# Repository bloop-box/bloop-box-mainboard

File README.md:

# Bloop Box Mainboard

[Documentation](https://bloop-box.github.io/bloop-box-mainboard)

The board is designed using KiCAD 6 with production and assembly by JLCPCB in mind. All parts are selected to be
available from JLCPCB at the time of writing and as many parts as possible are used from their basic library.

- uHAT format (fits on a Raspberry Pi Zero)
- Connectors for:
  - Tailboard (Power supply, buttons, LEDs)
  - SPI NFC-reader (Pinout fitting for *RC522* Module)
  - Speaker
  - I2C connector for LED-Board
  - Additional GPIO header with UART (optional)
- Speaker is driven by a MAX98357 3W amplifier
  - amplifier gain can be set through jumper (9dB default setting)
  - SD_MODE is set to stereo mix by default, solder jumper for setting left-only 

Pinout of all connectors is printed on the bottom of the board

See schematics for detailed GPIO pinout

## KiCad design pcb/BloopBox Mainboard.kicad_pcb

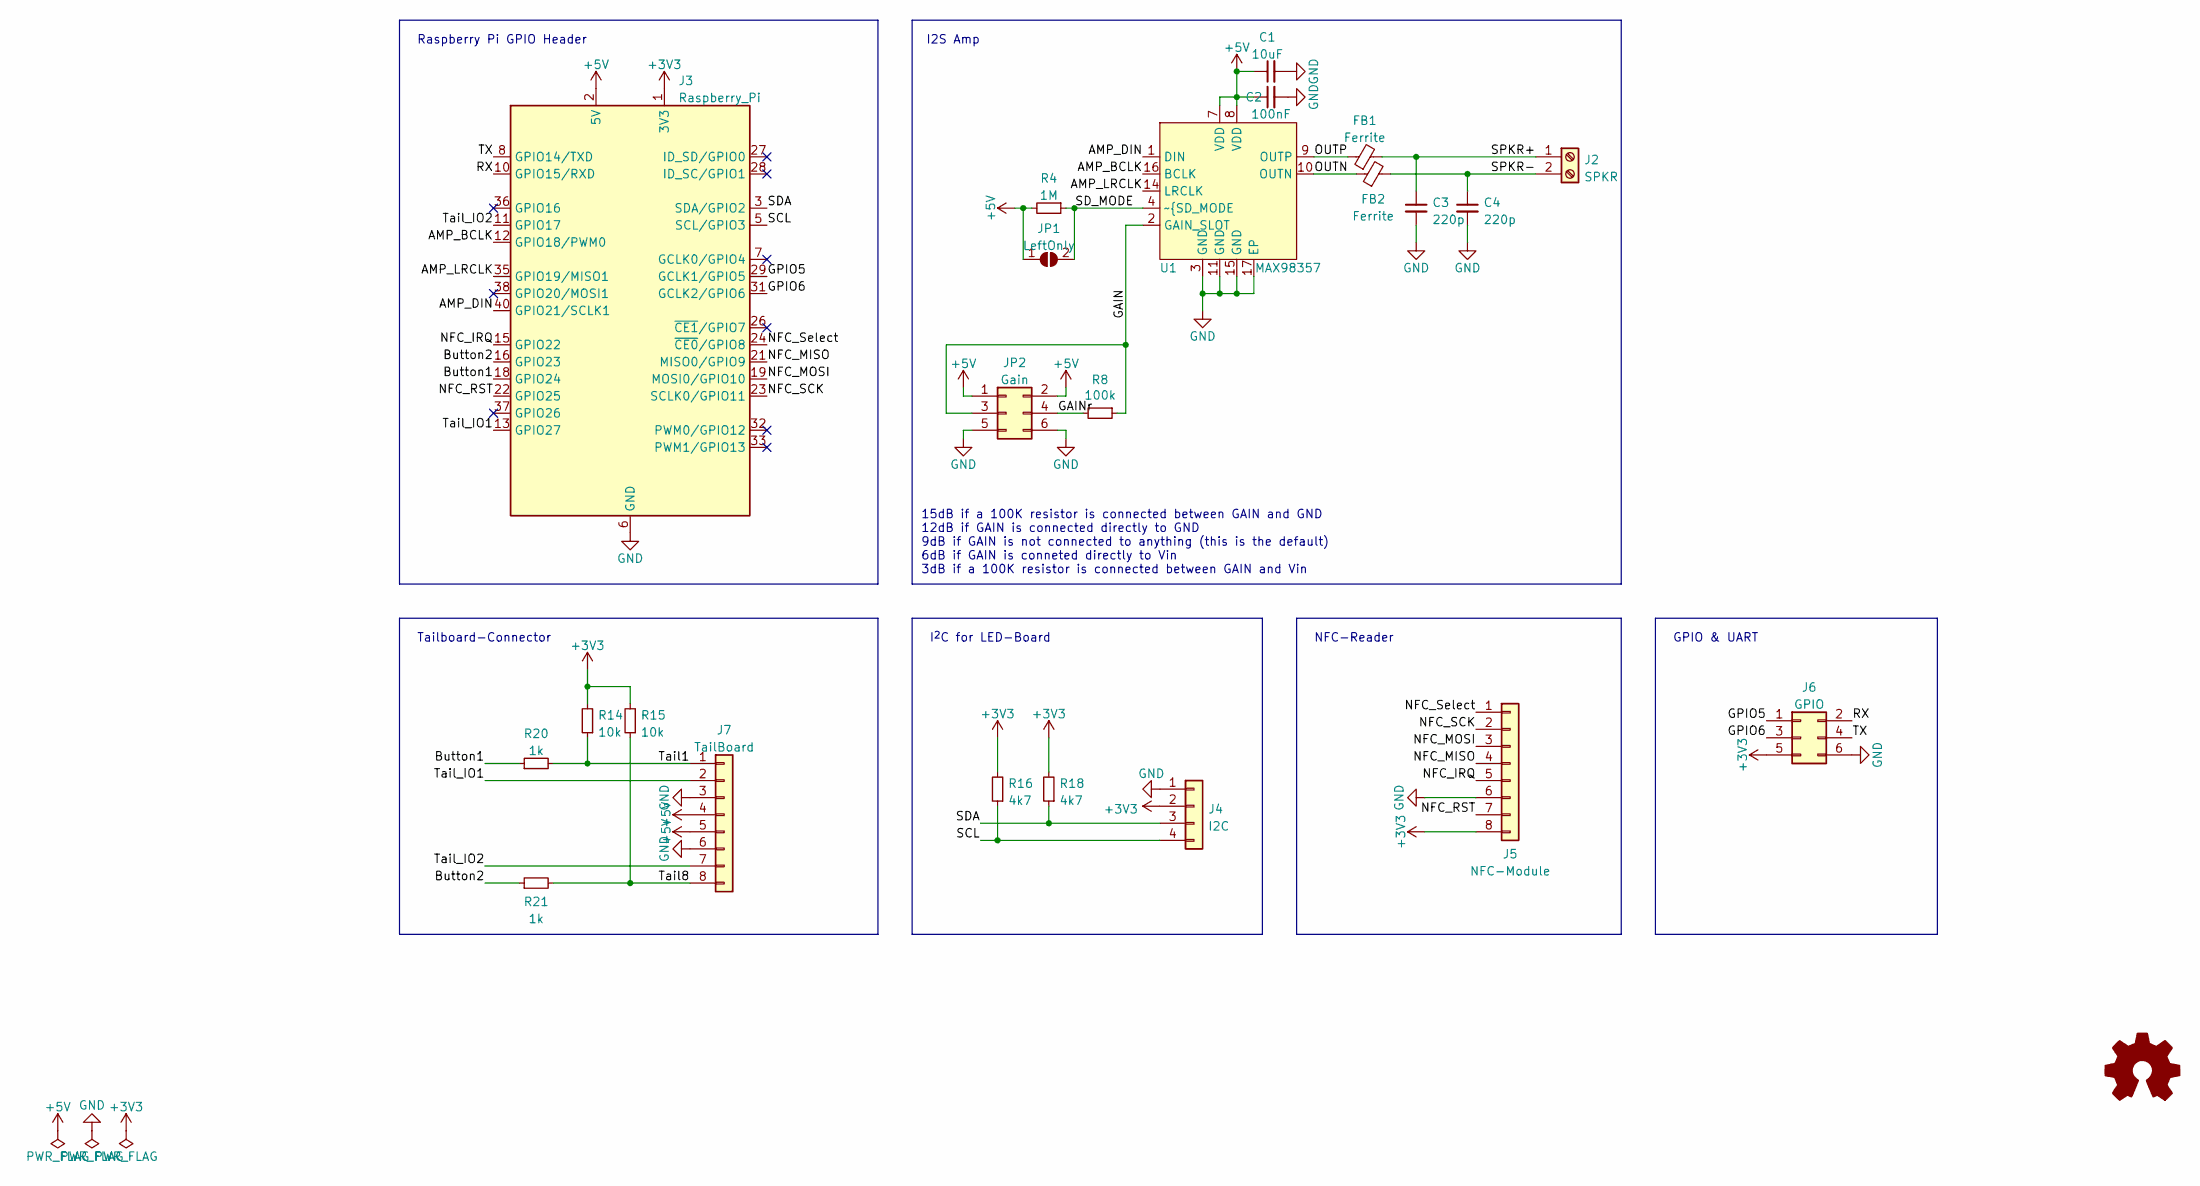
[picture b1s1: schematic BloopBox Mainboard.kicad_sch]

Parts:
C1: 10uF; C_0805_2012Metric; LCSC C15850
C2: 100nF; C_0402_1005Metric; LCSC C1525
C3, C4: 220p; C_0402_1005Metric; LCSC C1530
FB1, FB2: Ferrite; L_0805_2012Metric; LCSC C1015
J2: SPKR; JST_PH_S2B-PH-K_1x02_P2.00mm_Horizontal; LCSC C49992
J3: Raspberry_Pi; Raspberry_Pi_Zero_Socketed_THT_FaceDown_MountingHoles; LCSC C2977589
J4: I2C; JST_PH_S4B-PH-K_1x04_P2.00mm_Horizontal; LCSC C49994
J5: NFC-Module; JST_PH_S8B-PH-K_1x08_P2.00mm_Horizontal; LCSC C20598766
J6: GPIO; PinHeader_2x03_P2.54mm_Horizontal; LCSC C239334
J7: TailBoard; JST_PH_S8B-PH-K_1x08_P2.00mm_Horizontal; LCSC C20598766
JP1: LeftOnly; SolderJumper-2_P1.3mm_Open_RoundedPad1.0x1.5mm
JP2: Gain; PinHeader_2x03_P2.00mm_Vertical; LCSC C225288
R4: 1M; R_0402_1005Metric; LCSC C26083
R8: 100k; R_0402_1005Metric; LCSC C25741
R14, R15: 10k; R_0402_1005Metric; LCSC C25744
R16, R18: 4k7; R_0402_1005Metric; LCSC C25900
R20, R21: 1k; R_0402_1005Metric; LCSC C11702
U1: MAX98357; TQFN-16-1EP_3x3mm_P0.5mm_EP1.23x1.23mm_ThermalVias; LCSC C910544

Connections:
+3V3: J3.1 (3V3), J3.17 (3V3), J4.2, J5.8, J6.5, R14.2, R15.2, R16.2, R18.2
+5V: C1.1, C2.1, J3.2 (5V), J3.4 (5V), J7.4, J7.5, JP1.1 (A), JP2.1, JP2.2, R4.2, U1.7 (VDD), U1.8 (VDD)
/AMP_BCLK: J3.12 (GPIO18/PWM0), U1.16 (BCLK)
/AMP_DIN: J3.40 (GPIO21/SCLK1), U1.1 (DIN)
/AMP_LRCLK: J3.35 (GPIO19/MISO1), U1.14 (LRCLK)
/Button1: J3.18 (GPIO24), R20.1
/Button2: J3.16 (GPIO23), R21.1
/GAIN: JP2.3, R8.1, U1.2 (GAIN_SLOT)
/GAINr: JP2.4, R8.2
/GPIO5: J3.29 (GCLK1/GPIO5), J6.1
/GPIO6: J3.31 (GCLK2/GPIO6), J6.3
/NFC_IRQ: J3.15 (GPIO22), J5.5
/NFC_MISO: J3.21 (MISO0/GPIO9), J5.4
/NFC_MOSI: J3.19 (MOSI0/GPIO10), J5.3
/NFC_RST: J3.22 (GPIO25), J5.7
/NFC_SCK: J3.23 (SCLK0/GPIO11), J5.2
/NFC_Select: J3.24 (~CE0/GPIO8), J5.1
/OUTN: FB2.1, U1.10 (OUTN)
/OUTP: FB1.1, U1.9 (OUTP)
/RX: J3.10 (GPIO15/RXD), J6.2
/SCL: J3.5 (SCL/GPIO3), J4.4, R16.1
/SDA: J3.3 (SDA/GPIO2), J4.3, R18.1
/SD_MODE: JP1.2 (B), R4.1, U1.4 (~{SD_MODE)
/SPKR+: C3.1, FB1.2, J2.1
/SPKR-: C4.1, FB2.2, J2.2
/TX: J3.8 (GPIO14/TXD), J6.4
/Tail1: J7.1, R14.1, R20.2
/Tail8: J7.8, R15.1, R21.2
/Tail_IO1: J3.13 (GPIO27), J7.2
/Tail_IO2: J3.11 (GPIO17), J7.7
GND: C1.2, C2.2, C3.2, C4.2, J3.6 (GND), J3.9 (GND), J3.14 (GND), J3.20 (GND), J3.25 (GND), J3.30 (GND), J3.34 (GND), J3.39 (GND), J4.1, J5.6, J6.6, J7.3, J7.6, JP2.5, JP2.6, U1.3 (GND), U1.11 (GND), U1.15 (GND), U1.17 (EP)

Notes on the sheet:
I^{2}C for LED-Board
Raspberry Pi GPIO Header
GPIO & UART
I2S Amp
Tailboard-Connector
15dB if a 100K resistor is connected between GAIN and GND 12dB if GAIN is connected directly to GND 9dB if GAIN is not connected to anything (this is the default) 6dB if GAIN is conneted directly to Vin 3dB if a 100K resistor is connected between GAIN and Vin
NFC-Reader

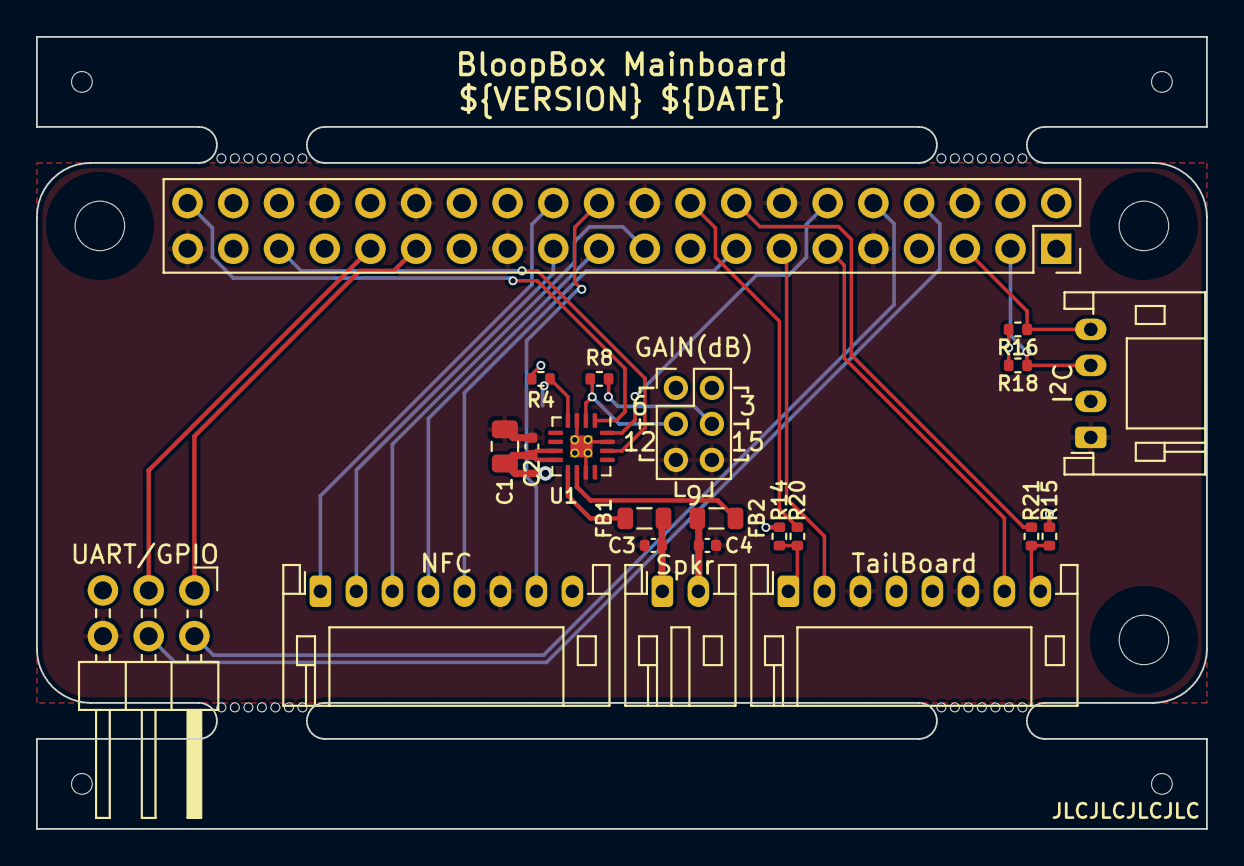
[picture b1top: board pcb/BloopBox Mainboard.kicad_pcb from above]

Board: 2 copper layers, 65.0 x 44.0 mm, 27 parts (1 on the bottom side), 31 nets.

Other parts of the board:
mouse-bite-2mm-slot, mouse-bite-2mm-slot#2, mouse-bite-2mm-slot#3, mouse-bite-2mm-slot#4: VAL**; mouse-bite-2x5mm-slot-onesided

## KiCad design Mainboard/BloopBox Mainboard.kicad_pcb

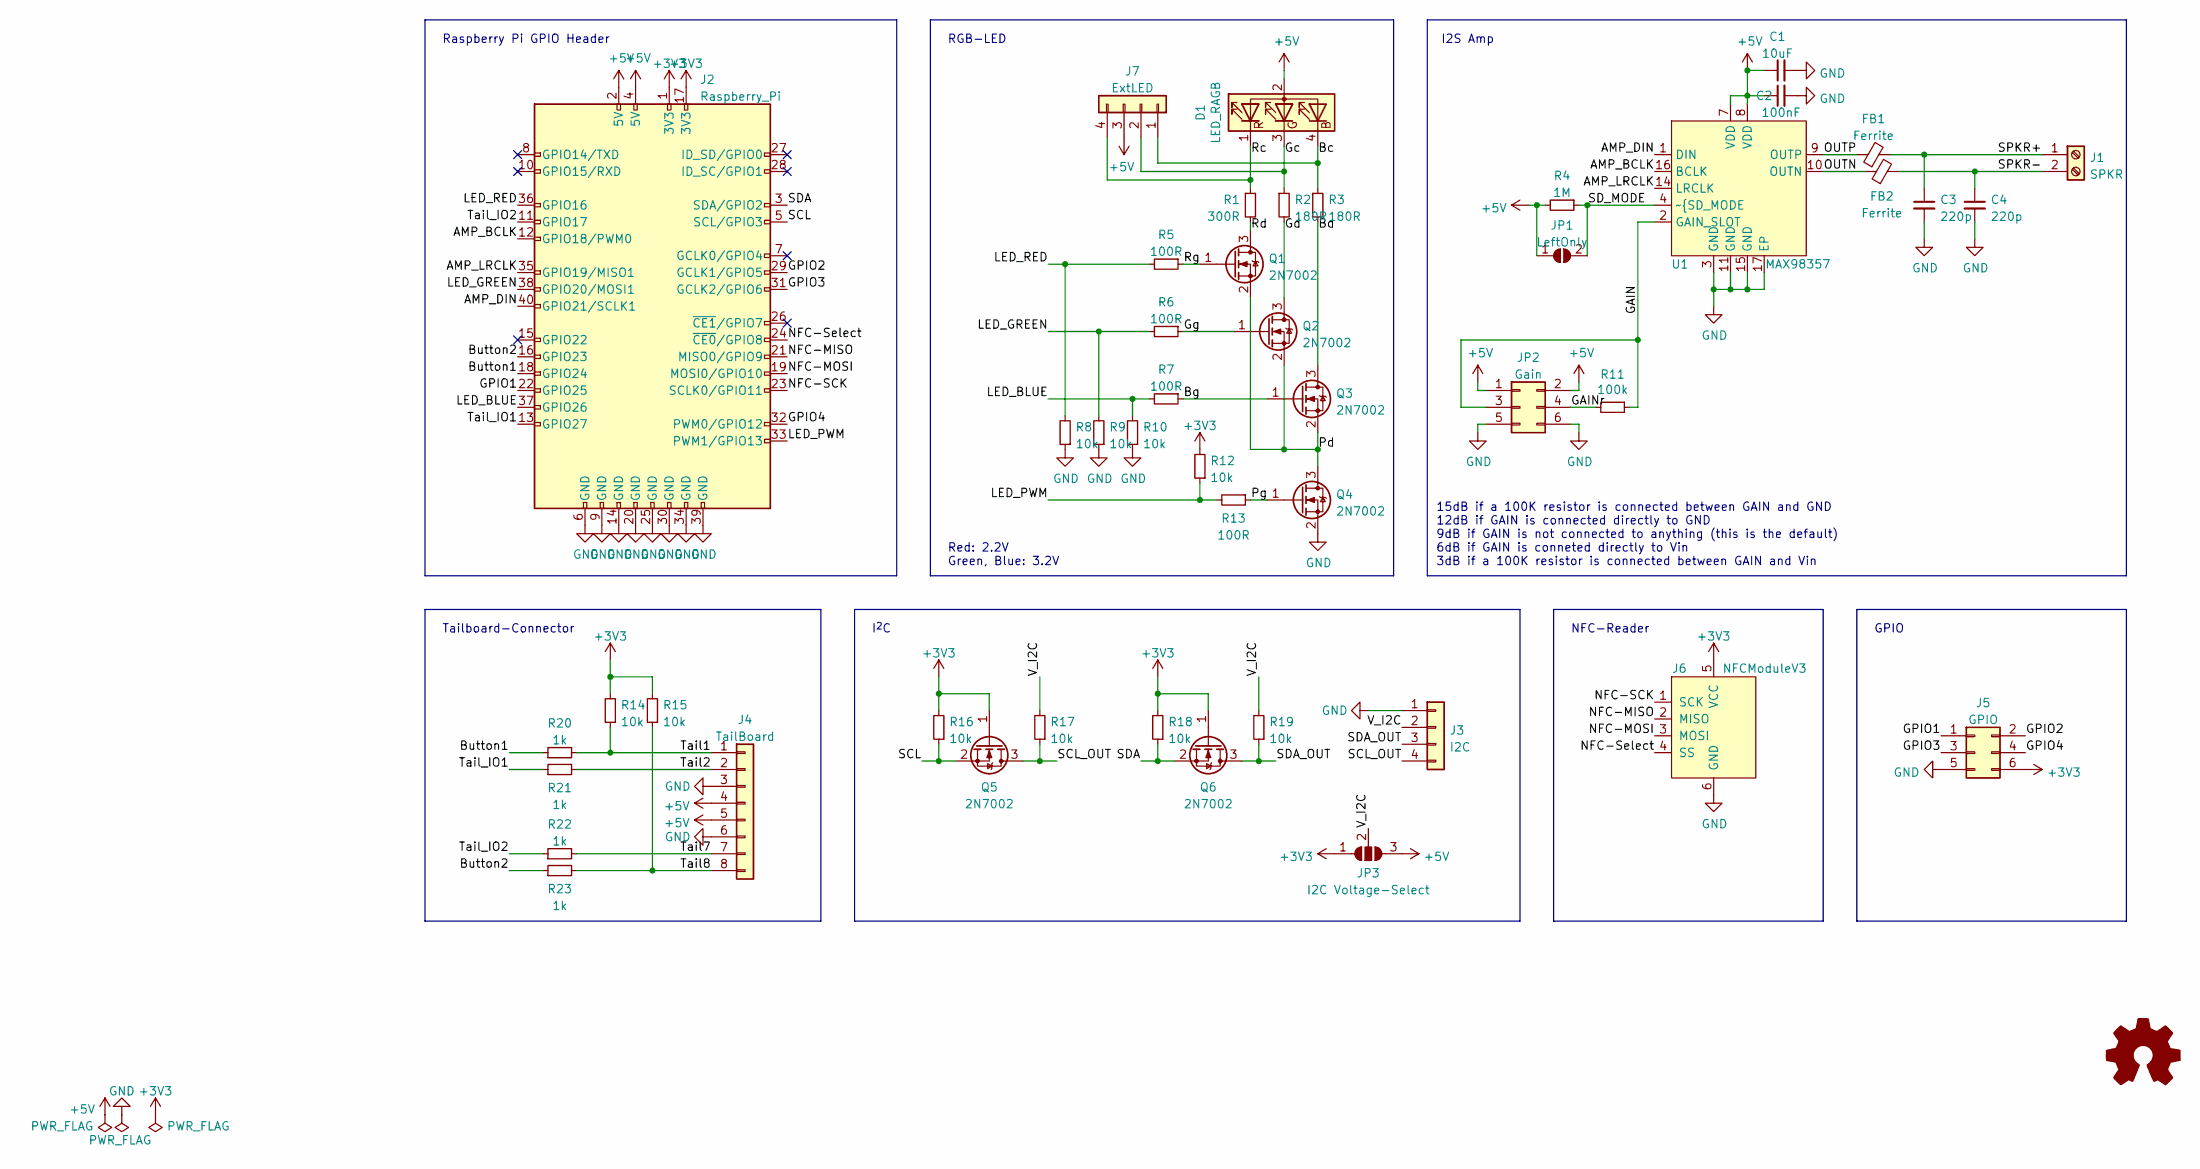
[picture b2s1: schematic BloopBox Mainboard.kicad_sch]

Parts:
C1: 10uF; C_0805_2012Metric; LCSC C15850
C2: 100nF; C_0402_1005Metric; LCSC C1525
C3, C4: 220p; C_0402_1005Metric; LCSC C1530
D1: LED_RAGB; LED_D5.0mm-4_RGB_Staggered_Pins
FB1, FB2: Ferrite; L_0805_2012Metric; LCSC C1015
J1: SPKR; JST_PH_S2B-PH-K_1x02_P2.00mm_Horizontal; LCSC C722769
J2: Raspberry_Pi; Raspberry_Pi_Zero_Socketed_THT_FaceDown_MountingHoles; LCSC C2977589
J3: I2C; JST_PH_S4B-PH-K_1x04_P2.00mm_Horizontal; LCSC C722777
J4: TailBoard; JST_PH_S8B-PH-K_1x08_P2.00mm_Horizontal; LCSC C722793
J5: GPIO; PinHeader_2x03_P2.54mm_Horizontal
J6: NFCModuleV3; JST_PH_S6B-PH-K_1x06_P2.00mm_Horizontal; LCSC C2908638
J7: ExtLED; JST_PH_S4B-PH-K_1x04_P2.00mm_Horizontal
JP1: LeftOnly; SolderJumper-2_P1.3mm_Open_RoundedPad1.0x1.5mm
JP2: Gain; PinHeader_2x03_P1.27mm_Vertical
JP3: I2C Voltage-Select; SolderJumper-3_P1.3mm_Open_RoundedPad1.0x1.5mm
Q1, Q2, Q3, Q4, Q5, Q6: 2N7002; SOT-23; LCSC C8545
R1: 300R; R_0603_1608Metric; LCSC C23025
R2, R3: 180R; R_0603_1608Metric; LCSC C22828
R4: 1M; R_0402_1005Metric; LCSC C26083
R5, R6, R7, R13: 100R; R_0402_1005Metric; LCSC C25076
R8, R9, R10, R12, R14, R15, R16, R17, R18, R19: 10k; R_0402_1005Metric; LCSC C25794
R11: 100k; R_0402_1005Metric; LCSC C25741
R20, R21, R22, R23: 1k; R_0402_1005Metric
U1: MAX98357; TQFN-16-1EP_3x3mm_P0.5mm_EP1.23x1.23mm_ThermalVias; LCSC C910544

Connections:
+3V3: J2.1 (3V3), J2.17 (3V3), J5.6, J6.5 (VCC), JP3.1 (A), Q5.1 (G), Q6.1 (G), R12.2, R14.2, R15.2, R16.2, R18.2
+5V: C1.1, C2.1, D1.2 (A), J2.2 (5V), J2.4 (5V), J4.4, J4.5, J7.3, JP1.1 (A), JP2.1, JP2.2, JP3.3 (B), R4.2, U1.7 (VDD), U1.8 (VDD)
/AMP_BCLK: J2.12 (GPIO18/PWM0), U1.16 (BCLK)
/AMP_DIN: J2.40 (GPIO21/SCLK1), U1.1 (DIN)
/AMP_LRCLK: J2.35 (GPIO19/MISO1), U1.14 (LRCLK)
/Bc: D1.4 (BK), J7.1, R3.1
/Bd: Q3.3 (D), R3.2
/Bg: Q3.1 (G), R7.1
/Button1: J2.18 (GPIO24), R20.1
/Button2: J2.16 (GPIO23), R23.1
/GAIN: JP2.3, R11.1, U1.2 (GAIN_SLOT)
/GAINr: JP2.4, R11.2
/GPIO1: J2.22 (GPIO25), J5.1
/GPIO2: J2.29 (GCLK1/GPIO5), J5.2
/GPIO3: J2.31 (GCLK2/GPIO6), J5.3
/GPIO4: J2.32 (PWM0/GPIO12), J5.4
/Gc: D1.3 (GK), J7.2, R2.1
/Gd: Q2.3 (D), R2.2
/Gg: Q2.1 (G), R6.1
/LED_BLUE: J2.37 (GPIO26), R7.2, R10.2
/LED_GREEN: J2.38 (GPIO20/MOSI1), R6.2, R9.2
/LED_PWM: J2.33 (PWM1/GPIO13), R12.1, R13.2
/LED_RED: J2.36 (GPIO16), R5.2, R8.2
/NFC-MISO: J2.21 (MISO0/GPIO9), J6.2 (MISO)
/NFC-MOSI: J2.19 (MOSI0/GPIO10), J6.3 (MOSI)
/NFC-SCK: J2.23 (SCLK0/GPIO11), J6.1 (SCK)
/NFC-Select: J2.24 (~CE0/GPIO8), J6.4 (SS)
/OUTN: FB2.1, U1.10 (OUTN)
/OUTP: FB1.1, U1.9 (OUTP)
/Pd: Q1.2 (S), Q2.2 (S), Q3.2 (S), Q4.3 (D)
/Pg: Q4.1 (G), R13.1
/Rc: D1.1 (RK), J7.4, R1.1
/Rd: Q1.3 (D), R1.2
/Rg: Q1.1 (G), R5.1
/SCL: J2.5 (SCL/GPIO3), Q5.2 (S), R16.1
/SCL_OUT: J3.4, Q5.3 (D), R17.1
/SDA: J2.3 (SDA/GPIO2), Q6.2 (S), R18.1
/SDA_OUT: J3.3, Q6.3 (D), R19.1
/SD_MODE: JP1.2 (B), R4.1, U1.4 (~{SD_MODE)
/SPKR+: C3.1, FB1.2, J1.1
/SPKR-: C4.1, FB2.2, J1.2
/Tail1: J4.1, R14.1, R20.2
/Tail2: J4.2, R21.2
/Tail7: J4.7, R22.2
/Tail8: J4.8, R15.1, R23.2
/Tail_IO1: J2.13 (GPIO27), R21.1
/Tail_IO2: J2.11 (GPIO17), R22.1
/V_I2C: J3.2, JP3.2 (C), R17.2, R19.2
GND: C1.2, C2.2, C3.2, C4.2, J2.6 (GND), J2.9 (GND), J2.14 (GND), J2.20 (GND), J2.25 (GND), J2.30 (GND), J2.34 (GND), J2.39 (GND), J3.1, J4.3, J4.6, J5.5, J6.6 (GND), JP2.5, JP2.6, Q4.2 (S), R8.1, R9.1, R10.1, U1.3 (GND), U1.11 (GND), U1.15 (GND), U1.17 (EP)

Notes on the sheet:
I^{2}C
Raspberry Pi GPIO Header
GPIO
I2S Amp
RGB-LED
Red: 2.2V Green, Blue: 3.2V
Tailboard-Connector
15dB if a 100K resistor is connected between GAIN and GND 12dB if GAIN is connected directly to GND 9dB if GAIN is not connected to anything (this is the default) 6dB if GAIN is conneted directly to Vin 3dB if a 100K resistor is connected between GAIN and Vin
NFC-Reader

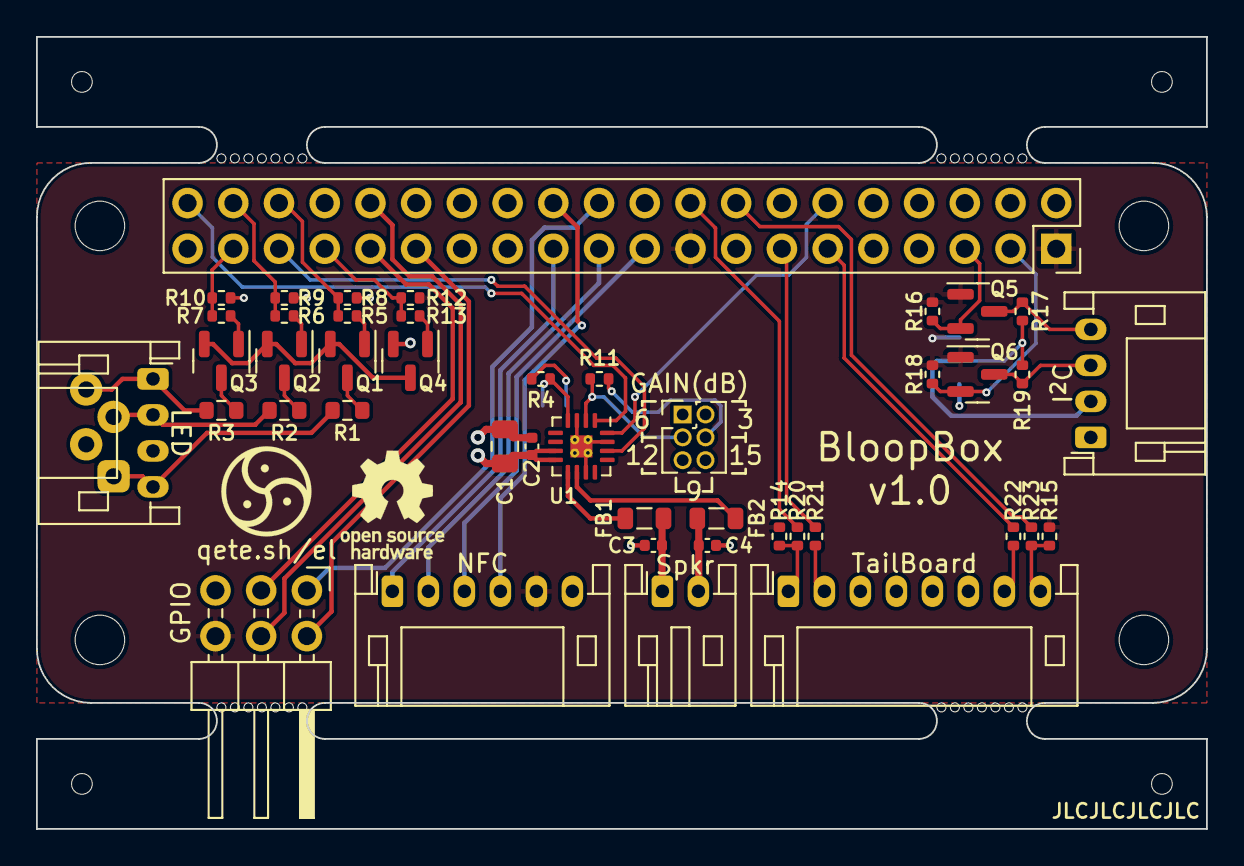
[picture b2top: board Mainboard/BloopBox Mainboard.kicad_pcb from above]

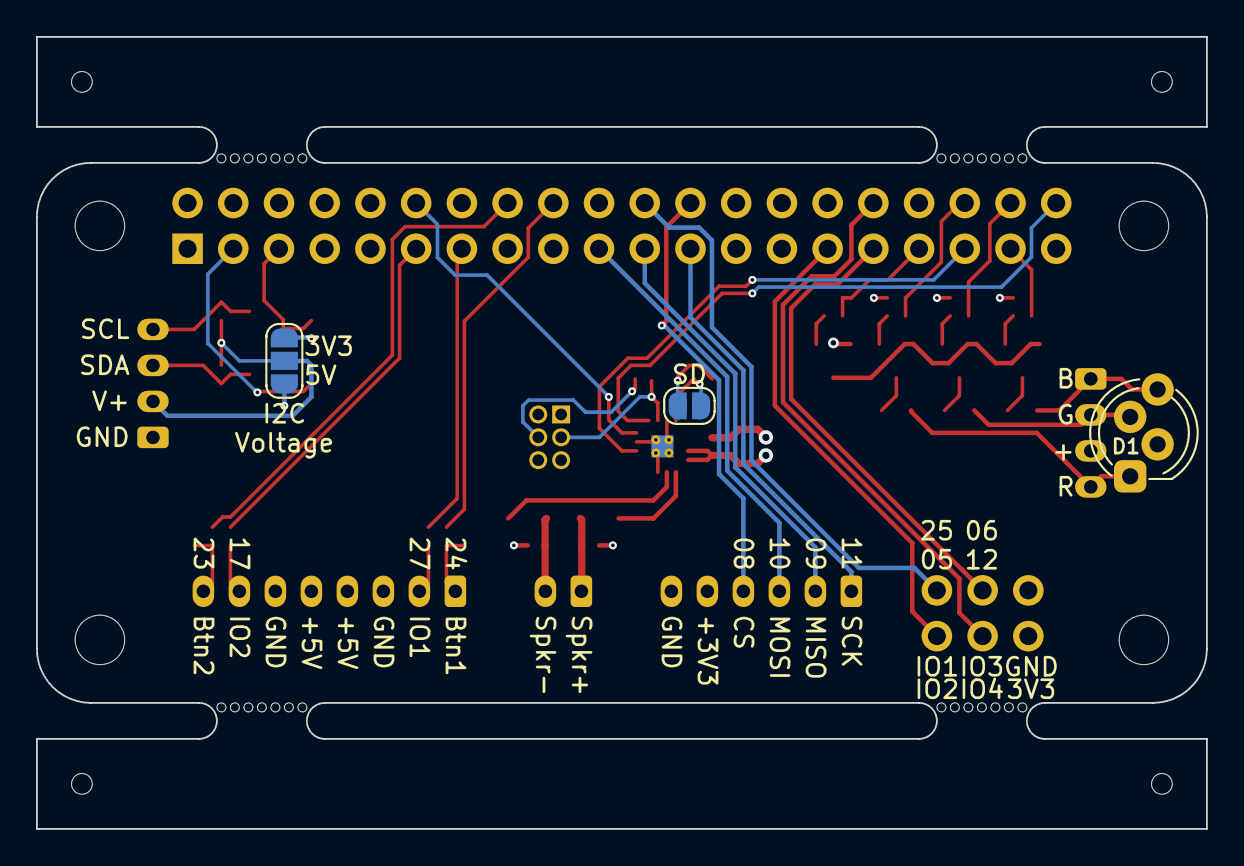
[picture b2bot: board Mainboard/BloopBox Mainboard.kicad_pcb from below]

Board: 4 copper layers, 65.0 x 44.0 mm, 51 parts (3 on the bottom side), 49 nets.

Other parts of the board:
mouse-bite-2mm-slot, mouse-bite-2mm-slot#2, mouse-bite-2mm-slot#3, mouse-bite-2mm-slot#4: VAL**; mouse-bite-2x5mm-slot-onesided

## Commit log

2022-12-01 Version 1.0
2022-12-02 Rename folders
2022-12-02 ci: add basic kibot workflow for mainboard
2022-12-02 ci: pass config-file to base workflow
2022-12-02 ci: add remaining boards to kibot
2022-12-02 docs: add CERN OHL-P license
2022-12-02 ci: update kibot.yml settings
2022-12-02 docs: add github status badges to README.md
2022-12-02 chore: remove .kicad_prl files from git
2022-12-02 docs: fill README with useful information
2022-12-03 docs: add details about NFC reader
2022-12-03 ci: add doc generation to GH pages repository
2022-12-03 ci: add missing type to kibot.yml
2022-12-03 ci: pass DOCS_DEPLOY_KEY secret down to reusable workflow
2022-12-03 ci: fix secret passing
2022-12-03 ci: refactor ci workflow
2022-12-03 ci: remove unused needs-dependency
2022-12-03 ci: fix name of input parameter
2022-12-03 ci: fix artifact deployment
2022-12-03 ci: add missing runs-on to deploy step
2022-12-03 ci: fix version of upload-pages-artifact action
2022-12-03 ci: add index.html file for navigate results
2022-12-03 docs: add renders and documentation links to README
2022-12-03 chore: add KiCAD autosave files to .gitignore
2022-12-03 feat: split mainboard into standalone repository
2022-12-03 ci: fix reference to reusable workflows
2022-12-03 ci: fix path filters
2022-12-03 ci: make docs job depend on check
2022-12-03 ci: fix board-file references
2022-12-04 chore: test CI workflow trigger
2022-12-04 ci: remove revision from docs output filenames
2022-12-04 ci: add release process
2022-12-04 build: rename layers to default names
2022-12-04 feat: prepare files for automatic version numbering
2022-12-04 ci: replace VERSION and DATE text variables on docs build
2022-12-04 fix: add DATE and VERSION text variables
2022-12-04 feat: more variables
    Using more variables to automate stuff
2022-12-04 ci: create release-please workflow
2022-12-04 ci: fix release-please yaml syntax
2022-12-04 ci: add missing permissions
2022-12-04 chore(main): release 1.0.0
2022-12-04 build: replace text variables on release
2022-12-04 ci: fix references to job output
2022-12-04 ci: use release kibot file on release
2022-12-04 ci: use reusable workflow for release-please
2022-12-05 style(workflows): add trailing newline
2022-12-05 chore: add BSD-2-Clause license for code
2022-12-05 feat: add UART to GPIO-Header
    Adding the UART TX and RX pins to the GPIO header for debugging console access
2022-12-09 fix: remove Tailboard IO protection resistors
    After removing the PD controller from the tailboard, the LEDs are directly connected to the mainboard so the protection resistors had to go
2022-12-12 feat!: change NFC connector to RC522 pinout
    Switch the NFC-connector from the PN532 module to the RC522 since the PN532 works not reliable with NTAG
    Connect IRQ and RST lines while doing so
2022-12-12 docs: update README
    NFC header changed to RC522
    UART added
2022-12-12 feat: add ID EEPROM
    Add (optional) ID EEPROM to the board that will allow some of the hardware to be auto-configured on the Raspberry Pi.
2022-12-13 feat: add initial eeprom settings and append compilation to release workflow
2022-12-13 ci: add eeprom workflow
2022-12-13 ci: add sudo to make install
2022-12-13 docs: add Eeprom badge
2022-12-13 ci: upload eeprom.eep artifact ater CI run
2023-01-03 docs: add info about eeprom
2023-01-03 feat: remove PWM mosfet
    didnt work as hoped so it gets removed
2023-01-03 fix: update nets
2023-01-03 fix: add default connection for I2C voltage jumper
2023-01-03 fix: 3d-model offset for GPIO connector
2023-01-18 feat!: remove RGB LED
    remove the RGB LED facilities since we're using I2C for that now
2023-01-19 style: remove disused silkscreen elements
2023-01-19 feat!: remove I2C level shifter
    The new LED driver needs 3.3V I2C anyway so the level shifter is not needed anymore.
2023-01-19 feat: reduce to two layers
    After removing some optional and deprecated hardware the board can be reduced to 2 layers to save production cost
2023-01-19 feat!: remove HAT EEPROM
    Since it is more effort to program each EEPROM after assembly than manually changing the settings it could handle, the EEPROM would only be a novelty and was removed.
2023-01-19 fix: change LCSC part number of I2C pullup
2023-01-19 docs: update Readme
2023-01-19 chore(main): release 2.0.0
2023-01-19 chore: remove EEPROM workflow
    The EEPROM was removed from the board, so we don't need the workflow and the settings file anymore.
2023-01-19 docs: clarify part selection process
2023-01-19 docs: remove EEPROM CI badge
2023-07-30 chore: update to KiCad 7
2024-07-31 chore: update to KiCad 8
2024-07-31 fix: copper edge clearance
2024-07-31 chore(main): release 2.0.1
2024-07-31 docs: remove wrong 3d model from footprint
2024-08-29 ci: remove dependency between jobs
